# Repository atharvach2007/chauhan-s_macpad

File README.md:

# Chauhan's Macropad
A macropad purpose built for me.
Built with Blueprint, Hackclub. It is a Macropad with 11 keys, a Rotary Encoder, 1 0.91 128x32 OLED and the SEEED XIAO RP2040.

### Images

### Specifications

BOM: 
- 11x Cherry MX Switches
- 1x XIAO RP2040
- 10x Blank DSA Keycaps
- 1x 0.91 128x32 OLED
- 1x EC11 Rotary Encoder
- 4x M3x16 Bolt
- 4x M3 Heatset

Others:
- KMK Firmware
- macpad_print_cover_new.stl
- macpad_print_plate_new.stl
- macpad_print_base_new.stl
- Custom PCB

Schematic            |  PCB
:-------------------------:|:-------------------------:|
     |

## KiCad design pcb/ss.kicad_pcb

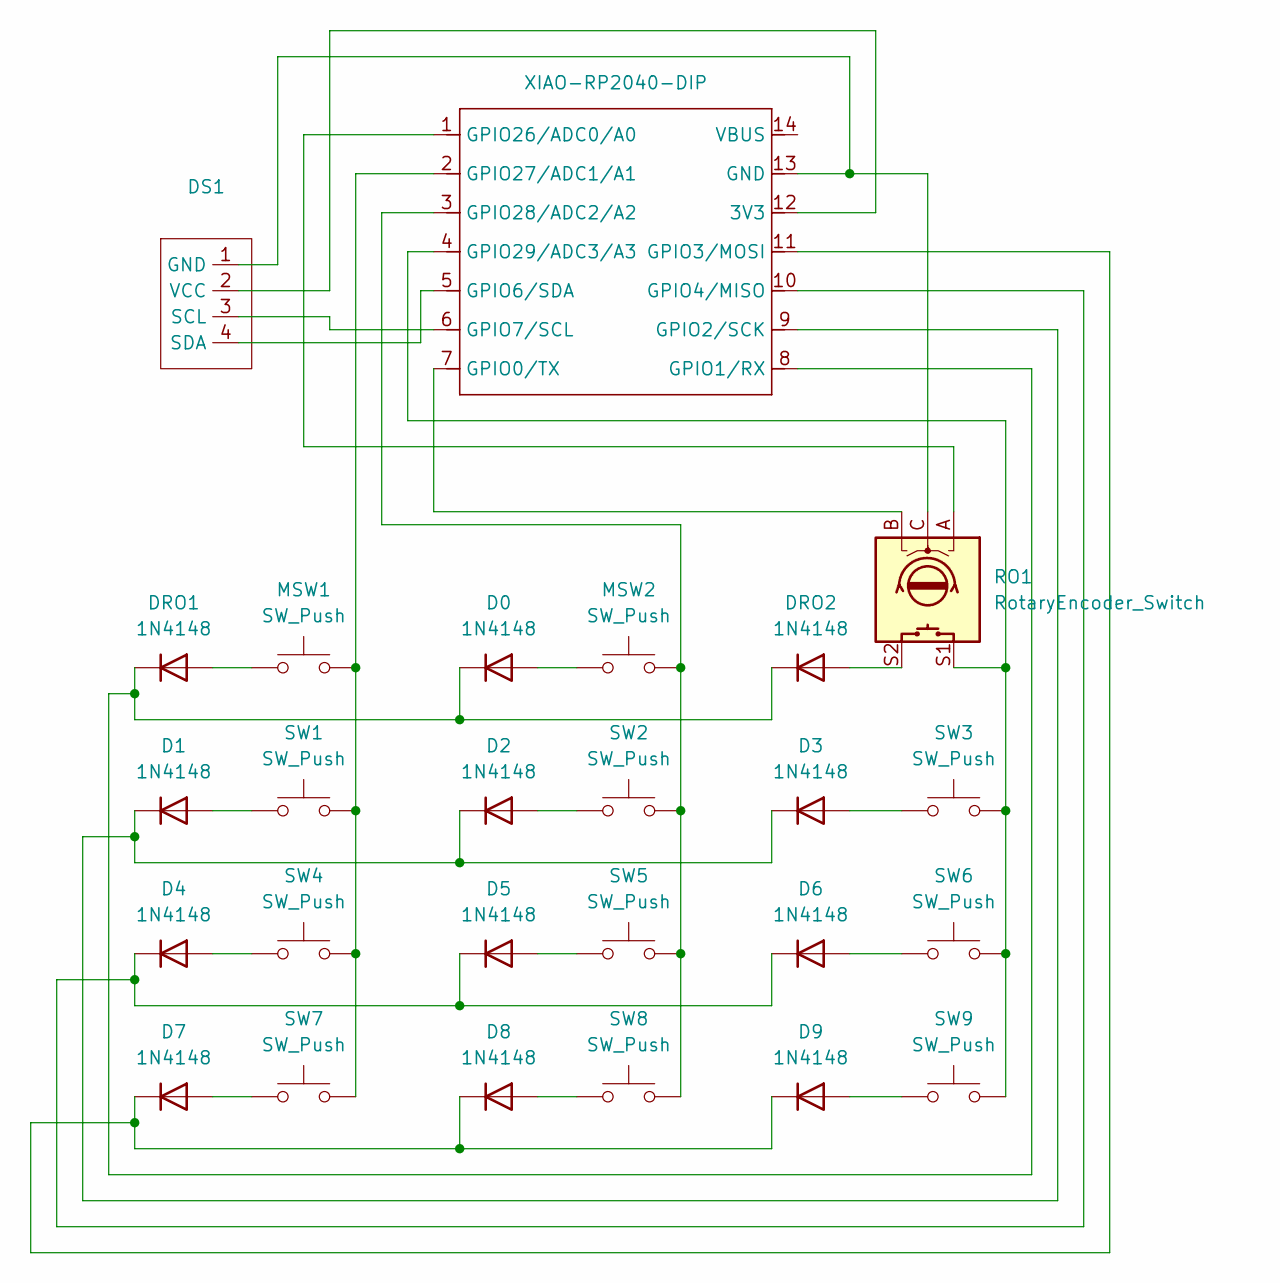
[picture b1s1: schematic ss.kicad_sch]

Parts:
D0, D1, D2, D3, D4, D5, D6, D7, D8, D9: 1N4148; D_DO-35_SOD27_P7.62mm_Horizontal
DRO1, DRO2: 1N4148; D_DO-35_SOD27_P7.62mm_Horizontal
DS1: SSD1306-0.91-OLED-4pin-128x32
MSW1, MSW2: SW_Push; SW_Cherry_MX_1.00u_PCB
RO1: RotaryEncoder_Switch; RotaryEncoder_Alps_EC11E-Switch_Vertical_H20mm
SW1, SW2, SW3, SW4, SW5, SW6, SW7, SW8, SW9: SW_Push; SW_Cherry_MX_1.00u_PCB
U1: XIAO-RP2040-DIP

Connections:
unnamed: D0.2 (A), MSW2.1
unnamed: D0.1 (K), DRO1.1 (K), DRO2.1 (K), U1.8 (GPIO1/RX)
unnamed: D1.2 (A), SW1.1
unnamed: D1.1 (K), D2.1 (K), D3.1 (K), U1.9 (GPIO2/SCK)
unnamed: D2.2 (A), SW2.1
unnamed: D3.2 (A), SW3.1
unnamed: D4.2 (A), SW4.1
unnamed: D4.1 (K), D5.1 (K), D6.1 (K), U1.10 (GPIO4/MISO)
unnamed: D5.2 (A), SW5.1
unnamed: D6.2 (A), SW6.1
unnamed: D7.2 (A), SW7.1
unnamed: D7.1 (K), D8.1 (K), D9.1 (K), U1.11 (GPIO3/MOSI)
unnamed: D8.2 (A), SW8.1
unnamed: D9.2 (A), SW9.1
unnamed: DRO1.2 (A), MSW1.1
unnamed: DRO2.2 (A), RO1.S2
unnamed: DS1.1 (GND), RO1.C, U1.13 (GND)
unnamed: DS1.3 (SCL), U1.6 (GPIO7/SCL)
unnamed: DS1.4 (SDA), U1.5 (GPIO6/SDA)
unnamed: DS1.2 (VCC), U1.12 (3V3)
unnamed: RO1.B, U1.7 (GPIO0/TX)
unnamed: RO1.A, U1.1 (GPIO26/ADC0/A0)
unnamed: MSW1.2, SW1.2, SW4.2, SW7.2, U1.2 (GPIO27/ADC1/A1)
unnamed: MSW2.2, SW2.2, SW5.2, SW8.2, U1.3 (GPIO28/ADC2/A2)
unnamed: RO1.S1, SW3.2, SW6.2, SW9.2, U1.4 (GPIO29/ADC3/A3)

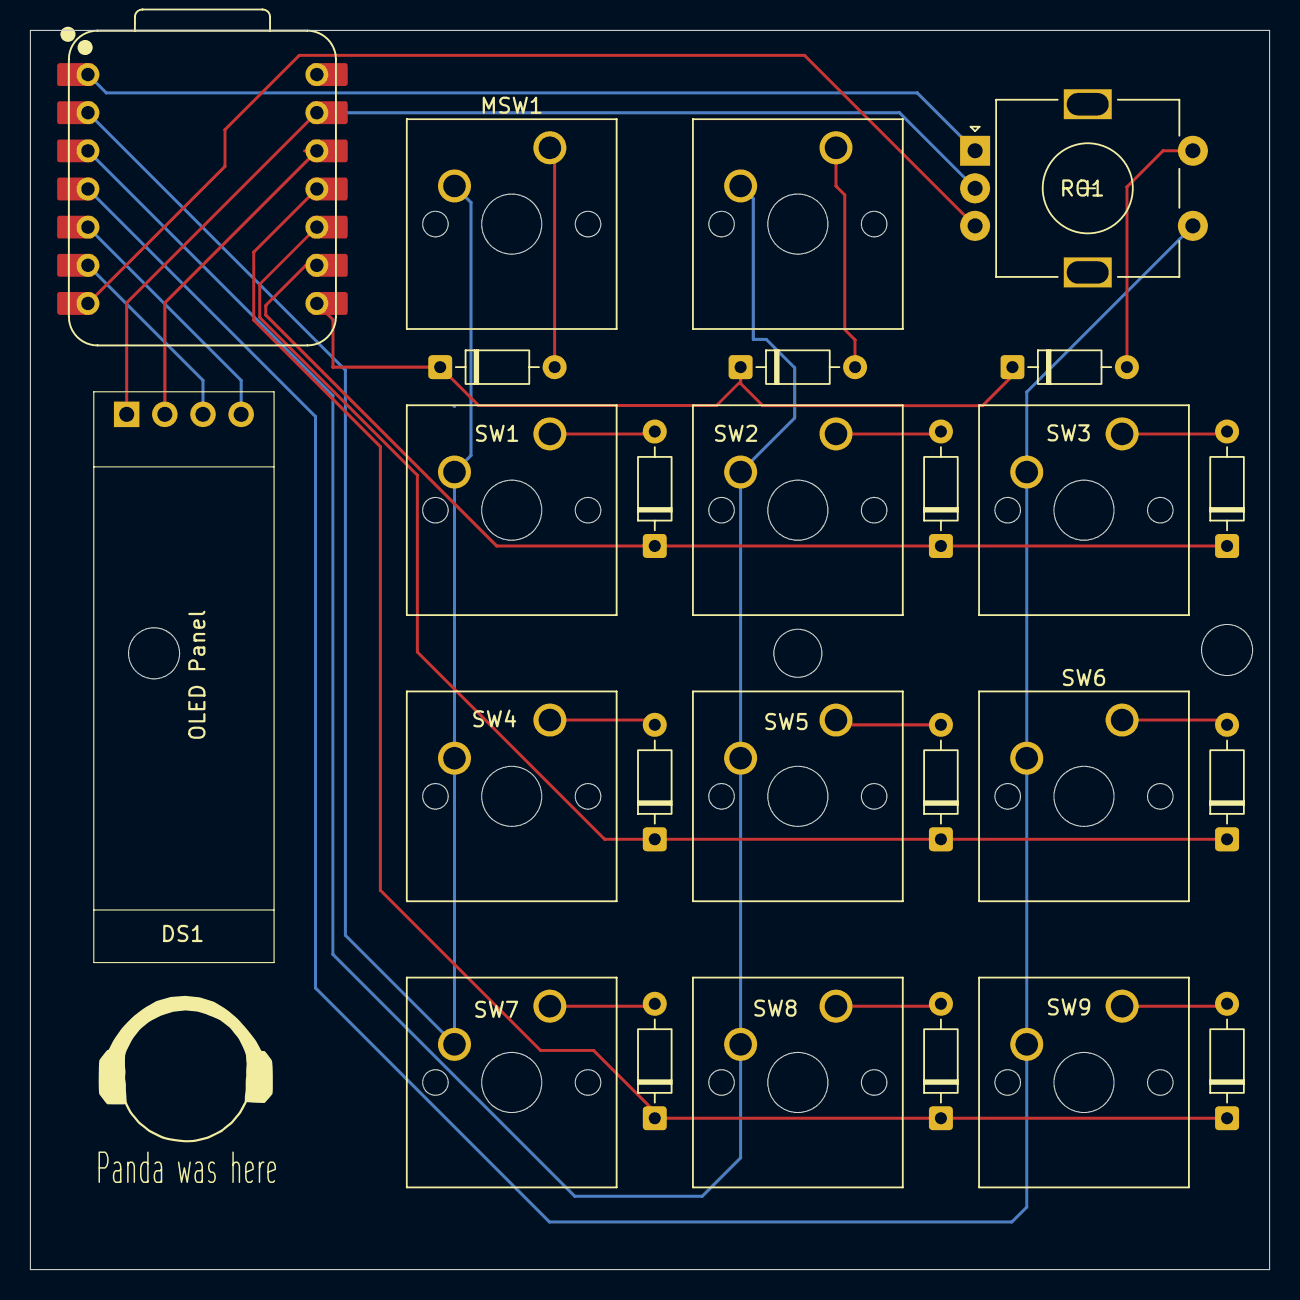
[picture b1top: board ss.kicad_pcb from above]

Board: 2 copper layers, 82.5 x 82.5 mm, 26 parts (0 on the bottom side), 25 nets.

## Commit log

2026-01-22 Updated main.py
2026-03-02 New Firmware
